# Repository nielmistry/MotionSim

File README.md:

# DIY Motion Simulator

This project provides a comprehensive guide to building a low-cost DIY motion simulator for flying RC planes and simulator games. Combining woodworking and mechatronics, it offers an affordable alternative to commercial options. The documentation includes CAD models, detailed assembly instructions, and software setup.

Support This Project: [Patreon](https://patreon.com/MichaelRechtin)

## Features
- Compatible with flight simulation games like Microsoft Flight Simulator 2020/2024 and WarThunder.
- Support for RC planes using ArduPilot.
- Modular design for portability, using a universal joint for base and chair connection.
- Open-source software and hardware design.

## Disclaimer
This is a DIY project; individual modifications may be necessary due to part availability or unique requirements. Ensure proper safety precautions, and consult professionals when needed. The author is not liable for any issues arising from the build.

## Getting Started
1. **CAD Models**: Access the full CAD design [here](https://cad.onshape.com/documents/14465a5308115755a641bf91/w/473302792caf9fe5237c9eca/e/42b5f99c290e18c70798f158?renderMode=0&uiState=67888ffc05482c0eb0b74d11).
2. **Bill of Materials**: Refer to the detailed parts list in the documentation for all required components.
3. **Tools Required**:
   - Saws (e.g., circular, jigsaw, CNC router)
   - Power drill, impact driver
   - Soldering iron, 3D printer

## Assembly
The simulator comprises two main parts:
- **Base Assembly**: Includes motor mounts, universal joint, and support structures.
- **Chair Assembly**: Features side panels, foot supports, and a universal joint for connection to the base.

Follow the detailed step-by-step instructions in the documentation.

## Electronics and Wiring
The wiring for the simulator includes:
- Motion base wiring for motors and drivers.
- Side compartment wiring for controller integration.
- Back panel connectors for ease of disassembly.

### Custom PCB Design
This repository includes a custom PCB design located in the `MotionSimPCB` directory that differs from the original project layout and provides several enhancements:

- **Power off button**: Integrated power control for safe system shutdown
- **Logic level translator**: Built-in voltage level conversion eliminating the need for external modules
- **Integrated MPU-6050 footprint**: Direct PCB mounting option for the motion sensor while maintaining compatibility with external MPU-6050 modules

The custom PCB maintains backward compatibility with the original wiring approach while offering a more integrated and robust solution.

Ensure proper orientation and connections for the MPU6050 sensor and other components.

## Software Setup
- **Teensy 4.0**: Flash the provided C++ code to control pitch and roll motors.
- **Raspberry Pi**: Configure USB flight controls and autorun scripts for seamless operation.
- **PC Integration**: Install necessary Python packages for supported games. Full code and instructions are available on the [GitHub repository](https://github.com/MichaelRechtin/MotionSim).

## Supported Games and Modes
- **Simulator Games**: Microsoft Flight Simulator 2020/2024, WarThunder
- **RC Planes**: Integration with Ardupilot and MAVLINK configurations

## Additional Features
- Optional integration with Buttkicker for enhanced gaming experience.
- Flexible wiring options for custom setups.

## Resources
- [Detailed Documentation](./DIY%20Motion%20Simulator%20Documentation.pdf)
- [PCB CI/CD Documentation](./docs/PCB_CI_CD.md) - Automated PCB manufacturing file generation
- [GitHub Repository](https://github.com/MichaelRechtin/MotionSim)
- [Bill of Materials](#)

### PCB Manufacturing

This repository includes automated CI/CD workflows for generating PCB manufacturing files:

- **Automated Gerber Generation**: Manufacturing files are automatically generated from KiCad PCB designs
- **Release Management**: Semantic versioning triggers automatic GitHub releases with PCB files
- **Local Generation**: Use `./generate-pcb-files.sh` to generate files locally

See [PCB CI/CD Documentation](./docs/PCB_CI_CD.md) for detailed information.

---

Feel free to explore, modify, and enjoy your DIY Motion Simulator!

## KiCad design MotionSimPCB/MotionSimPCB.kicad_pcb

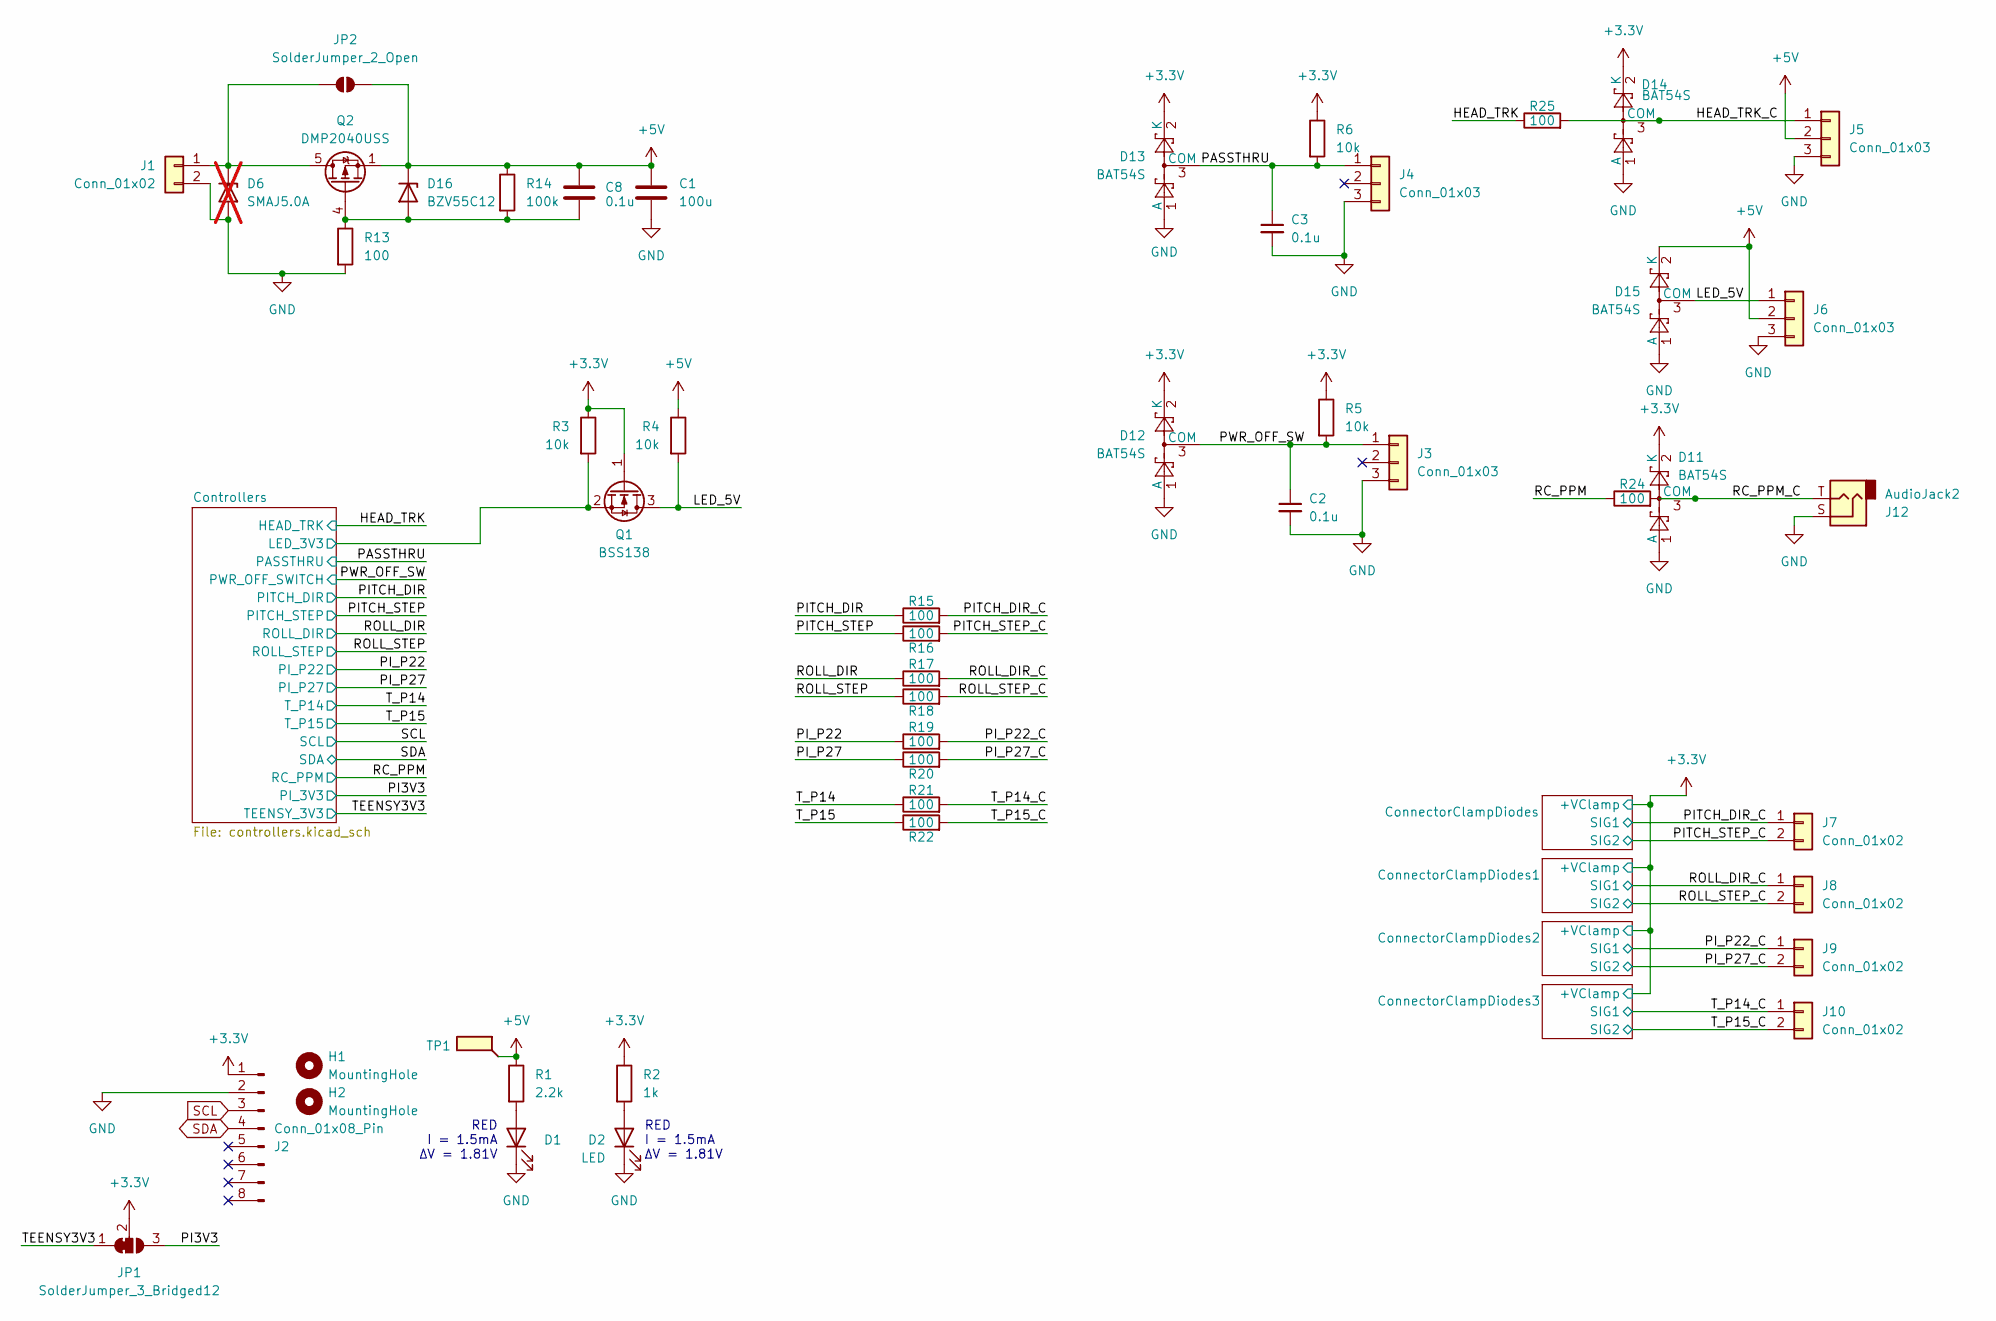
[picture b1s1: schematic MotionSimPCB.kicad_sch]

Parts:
C1: 100u; C_Radial_D6.3mm_H5.0mm_P2.50mm
C2, C3: 0.1u; C_0805_2012Metric
C8: 0.1u; C_0603_1608Metric
D1, D2: LED; D_0805_2012Metric; JLC PN C2286
D6: SMAJ5.0A; D_SMA; not fitted
D11, D12, D13, D14, D15: BAT54S; SOT-23
D16: BZV55C12; D_MiniMELF
H1, H2: MountingHole; MountingHole_2.7mm_M2.5
J1, J7, J8, J9, J10: Conn_01x02; TerminalBlock_Phoenix_MKDS-1,5-2_1x02_P5.00mm_Horizontal
J2: Conn_01x08_Pin; PinSocket_1x08_P2.54mm_Vertical
J3, J4, J5, J6: Conn_01x03; JST_XH_B3B-XH-AM_1x03_P2.50mm_Vertical
J12: AudioJack2
JP1: SolderJumper_3_Bridged12; SolderJumper-3_P1.3mm_Bridged2Bar12_RoundedPad1.0x1.5mm
JP2: SolderJumper_2_Open; SolderJumper-2_P1.3mm_Open_TrianglePad1.0x1.5mm
Q1: BSS138; SOT-23
Q2: DMP2040USS; SOIC-8_3.9x4.9mm_P1.27mm
R1: 2.2k; R_0805_2012Metric
R2: 1k; R_0805_2012Metric
R3, R4, R5, R6: 10k; R_0805_2012Metric
R13, R15, R16, R17, R18, R19, R20, R21, R22, R24, R25: 100; C_0603_1608Metric
R14: 100k; C_0603_1608Metric
TP1: TestPoint_Flag; TestPoint_Pad_D2.0mm

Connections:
+3.3V: D11.2 (K), D12.2 (K), D13.2 (K), D14.2 (K), J2.1, JP1.2 (C), Q1.1 (G), R2.1, R3.1, R5.1, R6.1; also elsewhere on the board
+5V: C1.1, C8.1, D15.2 (K), D16.1 (K), J5.2, J6.2, JP2.2 (B), Q2.1 (S), Q2.2 (S), Q2.3 (S), R1.1, R4.1, R14.1, TP1.1; also elsewhere on the board
/Controllers/LED_3V3: Q1.2 (S), R3.2; also elsewhere on the board
/HEAD_TRK: R25.1; also elsewhere on the board
/HEAD_TRK_C: D14.3 (COM), J5.1, R25.2
/LED_5V: D15.3 (COM), J6.1, Q1.3 (D), R4.2
/PASSTHRU: C3.1, D13.3 (COM), J4.1, R6.2; also elsewhere on the board
/PI3V3: JP1.3 (B); also elsewhere on the board
/PITCH_DIR: R15.1; also elsewhere on the board
/PITCH_DIR_C: J7.1, R15.2; also elsewhere on the board
/PITCH_STEP: R16.1; also elsewhere on the board
/PITCH_STEP_C: J7.2, R16.2; also elsewhere on the board
/PI_P22: R19.1; also elsewhere on the board
/PI_P22_C: J9.1, R19.2; also elsewhere on the board
/PI_P27: R20.1; also elsewhere on the board
/PI_P27_C: J9.2, R20.2; also elsewhere on the board
/PWR_OFF_SW: C2.1, D12.3 (COM), J3.1, R5.2; also elsewhere on the board
/RC_PPM: R24.1; also elsewhere on the board
/RC_PPM_C: D11.3 (COM), J12.T, R24.2
/ROLL_DIR: R17.1; also elsewhere on the board
/ROLL_DIR_C: J8.1, R17.2; also elsewhere on the board
/ROLL_STEP: R18.1; also elsewhere on the board
/ROLL_STEP_C: J8.2, R18.2; also elsewhere on the board
/TEENSY3V3: JP1.1 (A); also elsewhere on the board
/T_P14: R21.1; also elsewhere on the board
/T_P14_C: J10.1, R21.2; also elsewhere on the board
/T_P15: R22.1; also elsewhere on the board
/T_P15_C: J10.2, R22.2; also elsewhere on the board
GND: C1.2, C2.2, C3.2, D1.1 (K), D2.1 (K), D6.2 (A2), D11.1 (A), D12.1 (A), D13.1 (A), D14.1 (A), D15.1 (A), J1.2, J2.2, J3.3, J4.3, J5.3, J6.3, J12.S, R13.2; also elsewhere on the board
unnamed: D1.2 (A), R1.2
unnamed: D2.2 (A), R2.2
unnamed: D6.1 (A1), J1.1, JP2.1 (A), Q2.5 (D), Q2.6 (D), Q2.7 (D), Q2.8 (D)
unnamed: C8.2, D16.2 (A), Q2.4 (G), R13.1, R14.2
SCL: J2.3; also elsewhere on the board
SDA: J2.4; also elsewhere on the board

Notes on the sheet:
RED I = 1.5mA ΔV = 1.81V

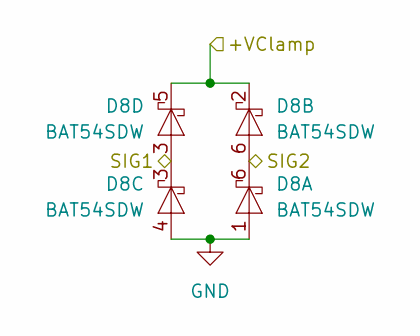
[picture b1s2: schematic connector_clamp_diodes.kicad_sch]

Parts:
D8: BAT54SDW; SOT-363_SC-70-6

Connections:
+3.3V: D8.2 (K), D8.5 (K); also elsewhere on the board
/PITCH_DIR_C: D8.3 (K); also elsewhere on the board
/PITCH_STEP_C: D8.6 (K); also elsewhere on the board
GND: D8.1 (A), D8.4 (A); also elsewhere on the board

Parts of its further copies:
D7, D9, D10: BAT54SDW; SOT-363_SC-70-6

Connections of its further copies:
+3.3V: D7.2 (K), D7.5 (K), D9.2 (K), D9.5 (K), D10.2 (K), D10.5 (K); also elsewhere on the board
/PI_P22_C: D9.3 (K); also elsewhere on the board
/PI_P27_C: D9.6 (K); also elsewhere on the board
/ROLL_DIR_C: D7.3 (K); also elsewhere on the board
/ROLL_STEP_C: D7.6 (K); also elsewhere on the board
/T_P14_C: D10.3 (K); also elsewhere on the board
/T_P15_C: D10.6 (K); also elsewhere on the board
GND: D7.1 (A), D7.4 (A), D9.1 (A), D9.4 (A), D10.1 (A), D10.4 (A); also elsewhere on the board

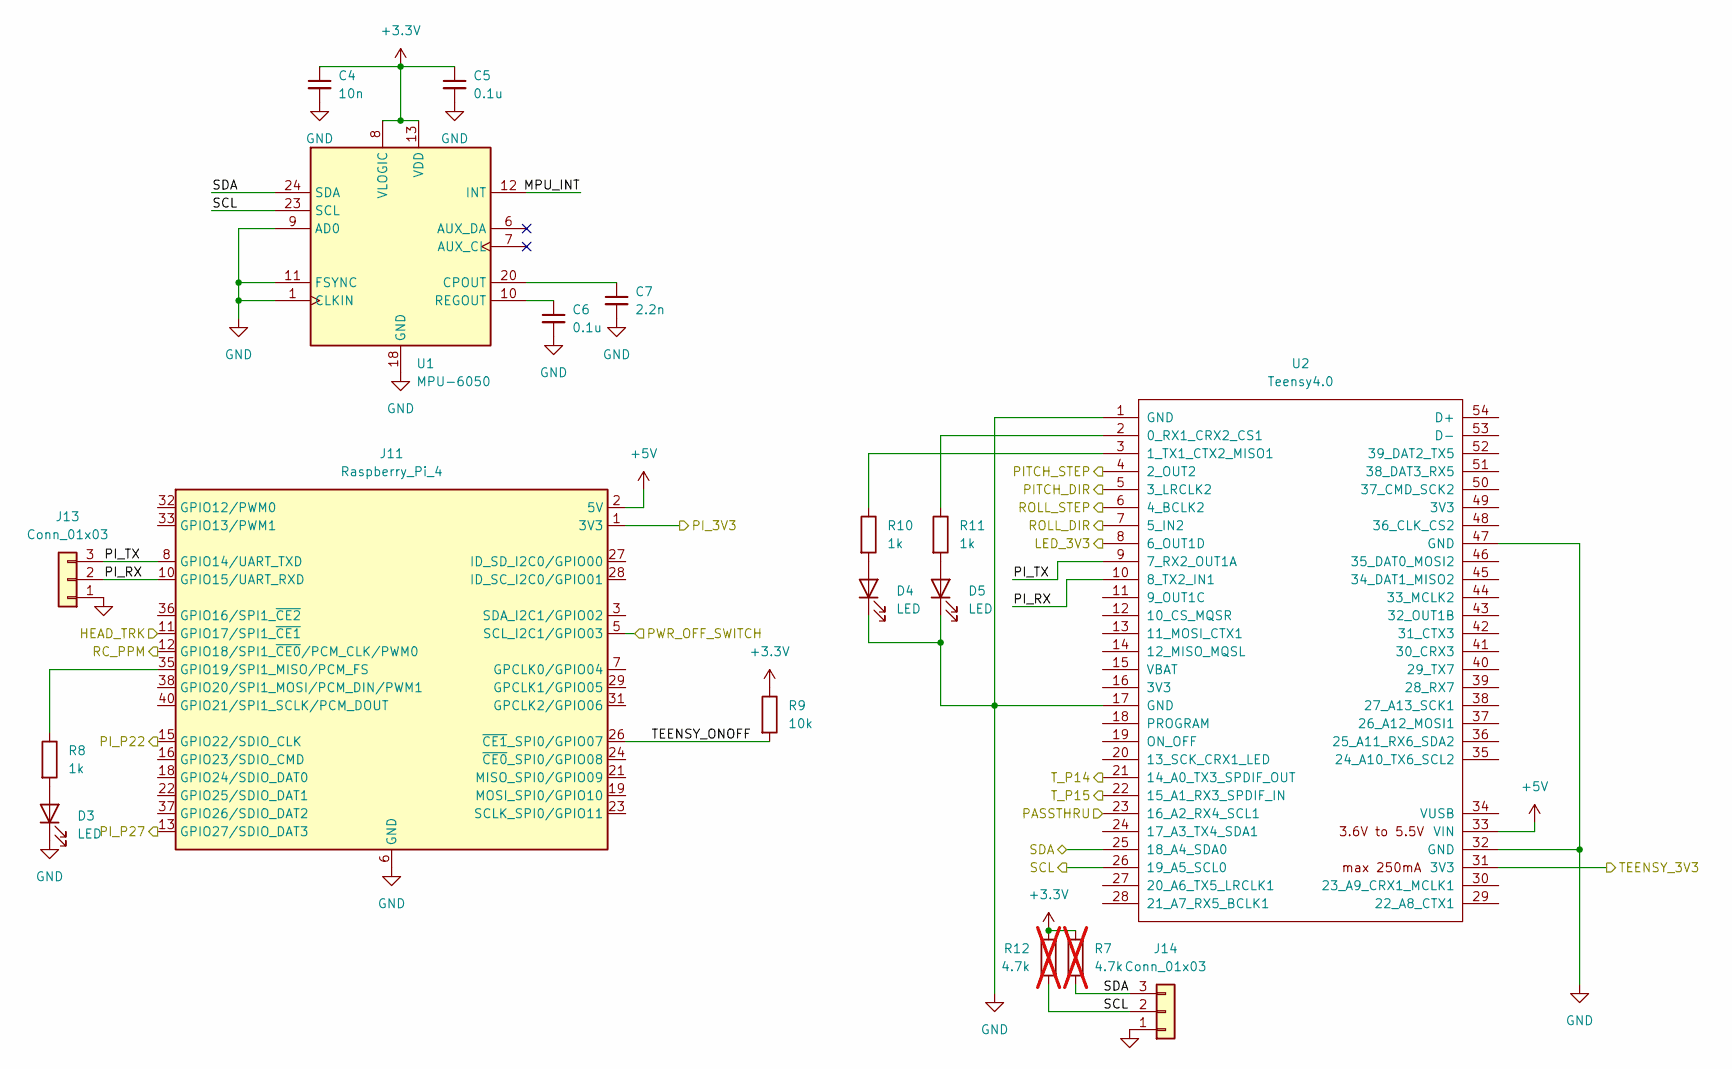
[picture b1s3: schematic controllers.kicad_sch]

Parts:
C4: 10n; C_0603_1608Metric
C5, C6: 0.1u; C_0603_1608Metric
C7: 2.2n; C_0603_1608Metric
D3, D4, D5: LED; D_0805_2012Metric; JLC PN C2289
J11: Raspberry_Pi_4; raspberrypi_2_3
J13, J14: Conn_01x03; PinHeader_1x03_P2.54mm_Vertical
R7, R12: 4.7k; R_0805_2012Metric; not fitted
R8, R10, R11: 1k; R_0805_2012Metric
R9: 10k; R_0805_2012Metric
U1: MPU-6050; InvenSense_QFN-24_4x4mm_P0.5mm
U2: Teensy4.0; Teensy40

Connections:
+3.3V: C4.1, C5.1, R7.1, R9.1, R12.1, U1.8 (VLOGIC), U1.13 (VDD); also elsewhere on the board
+5V: J11.2 (5V), J11.4 (5V), U2.33 (VIN); also elsewhere on the board
/Controllers/LED_3V3: U2.8 (6_OUT1D); also elsewhere on the board
/Controllers/MPU_INT: U1.12 (INT)
/Controllers/PI_RX: J11.10 (GPIO15/UART_RXD), J13.2, U2.10 (8_TX2_IN1)
/Controllers/PI_TX: J11.8 (GPIO14/UART_TXD), J13.3, U2.9 (7_RX2_OUT1A)
/Controllers/TEENSY_ONOFF: J11.26 (~CE1_SPI0/GPIO07), R9.2
/HEAD_TRK: J11.11 (GPIO17/SPI1_~CE1); also elsewhere on the board
/PASSTHRU: U2.23 (16_A2_RX4_SCL1); also elsewhere on the board
/PI3V3: J11.1 (3V3), J11.17 (3V3); also elsewhere on the board
/PITCH_DIR: U2.5 (3_LRCLK2); also elsewhere on the board
/PITCH_STEP: U2.4 (2_OUT2); also elsewhere on the board
/PI_P22: J11.15 (GPIO22/SDIO_CLK); also elsewhere on the board
/PI_P27: J11.13 (GPIO27/SDIO_DAT3); also elsewhere on the board
/PWR_OFF_SW: J11.5 (SCL_I2C1/GPIO03); also elsewhere on the board
/RC_PPM: J11.12 (GPIO18/SPI1_~CE0/PCM_CLK/PWM0); also elsewhere on the board
/ROLL_DIR: U2.7 (5_IN2); also elsewhere on the board
/ROLL_STEP: U2.6 (4_BCLK2); also elsewhere on the board
/TEENSY3V3: U2.31 (3V3); also elsewhere on the board
/T_P14: U2.21 (14_A0_TX3_SPDIF_OUT); also elsewhere on the board
/T_P15: U2.22 (15_A1_RX3_SPDIF_IN); also elsewhere on the board
GND: C4.2, C5.2, C6.2, C7.2, D3.1 (K), D4.1 (K), D5.1 (K), J11.6 (GND), J11.9 (GND), J11.14 (GND), J11.20 (GND), J11.25 (GND), J11.30 (GND), J11.34 (GND), J11.39 (GND), J13.1, J14.1, U1.1 (CLKIN), U1.9 (AD0), U1.11 (FSYNC), U1.18 (GND), U2.1 (GND), U2.17 (GND), U2.32 (GND), U2.47 (GND); also elsewhere on the board
unnamed: D3.2 (A), R8.2
unnamed: D4.2 (A), R10.2
unnamed: D5.2 (A), R11.2
unnamed: J11.35 (GPIO19/SPI1_MISO/PCM_FS), R8.1
unnamed: C7.1, U1.20 (CPOUT)
unnamed: C6.1, U1.10 (REGOUT)
unnamed: R11.1, U2.2 (0_RX1_CRX2_CS1)
unnamed: R10.1, U2.3 (1_TX1_CTX2_MISO1)
SCL: J14.2, R12.2, U1.23 (SCL), U2.26 (19_A5_SCL0); also elsewhere on the board
SDA: J14.3, R7.2, U1.24 (SDA), U2.25 (18_A4_SDA0); also elsewhere on the board

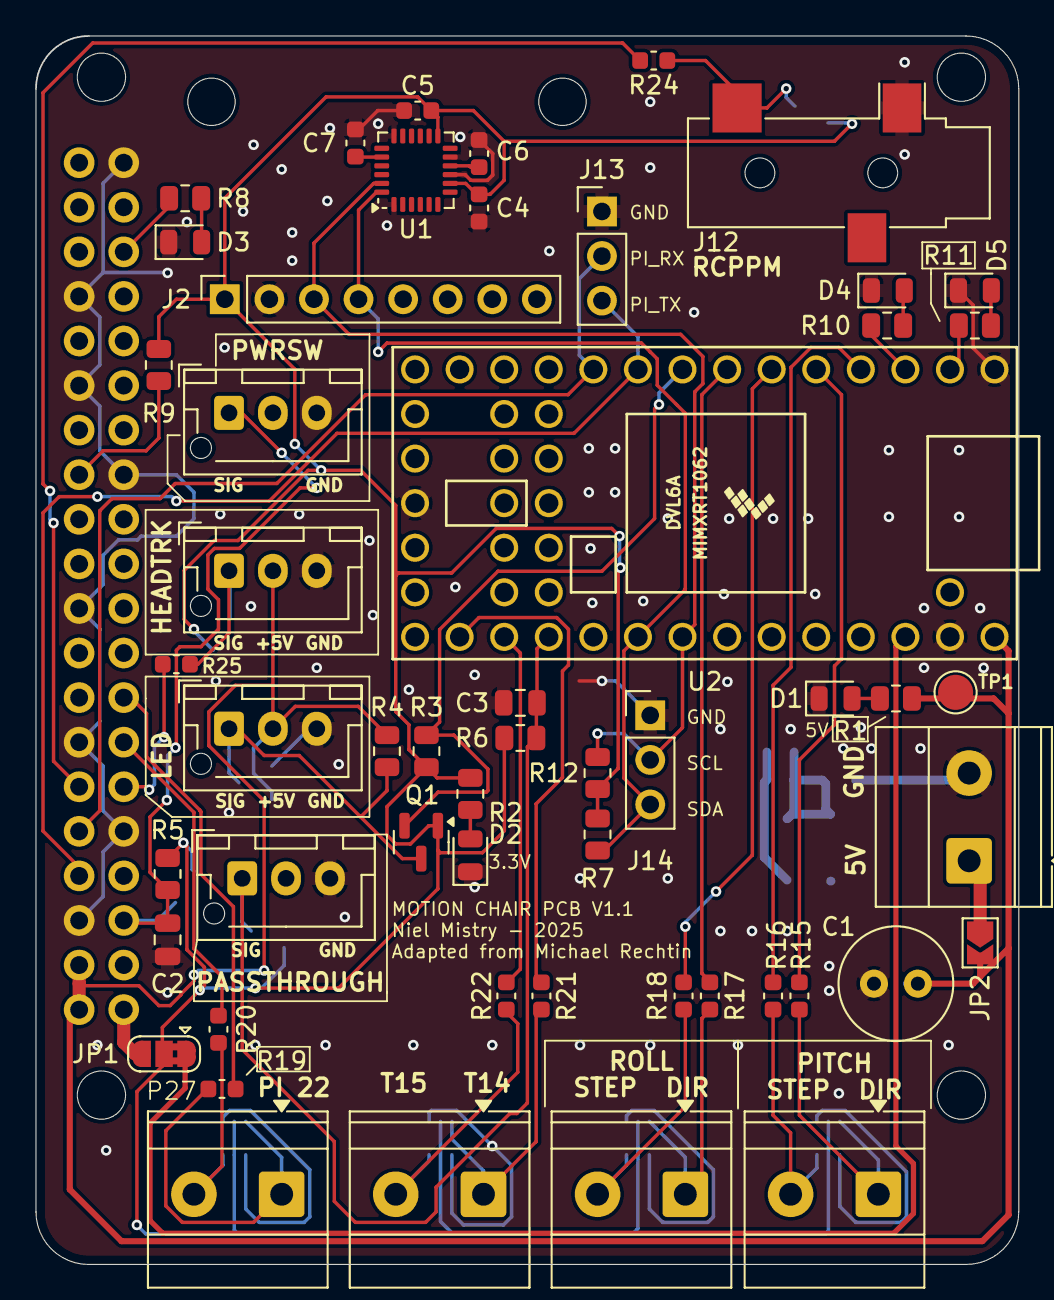
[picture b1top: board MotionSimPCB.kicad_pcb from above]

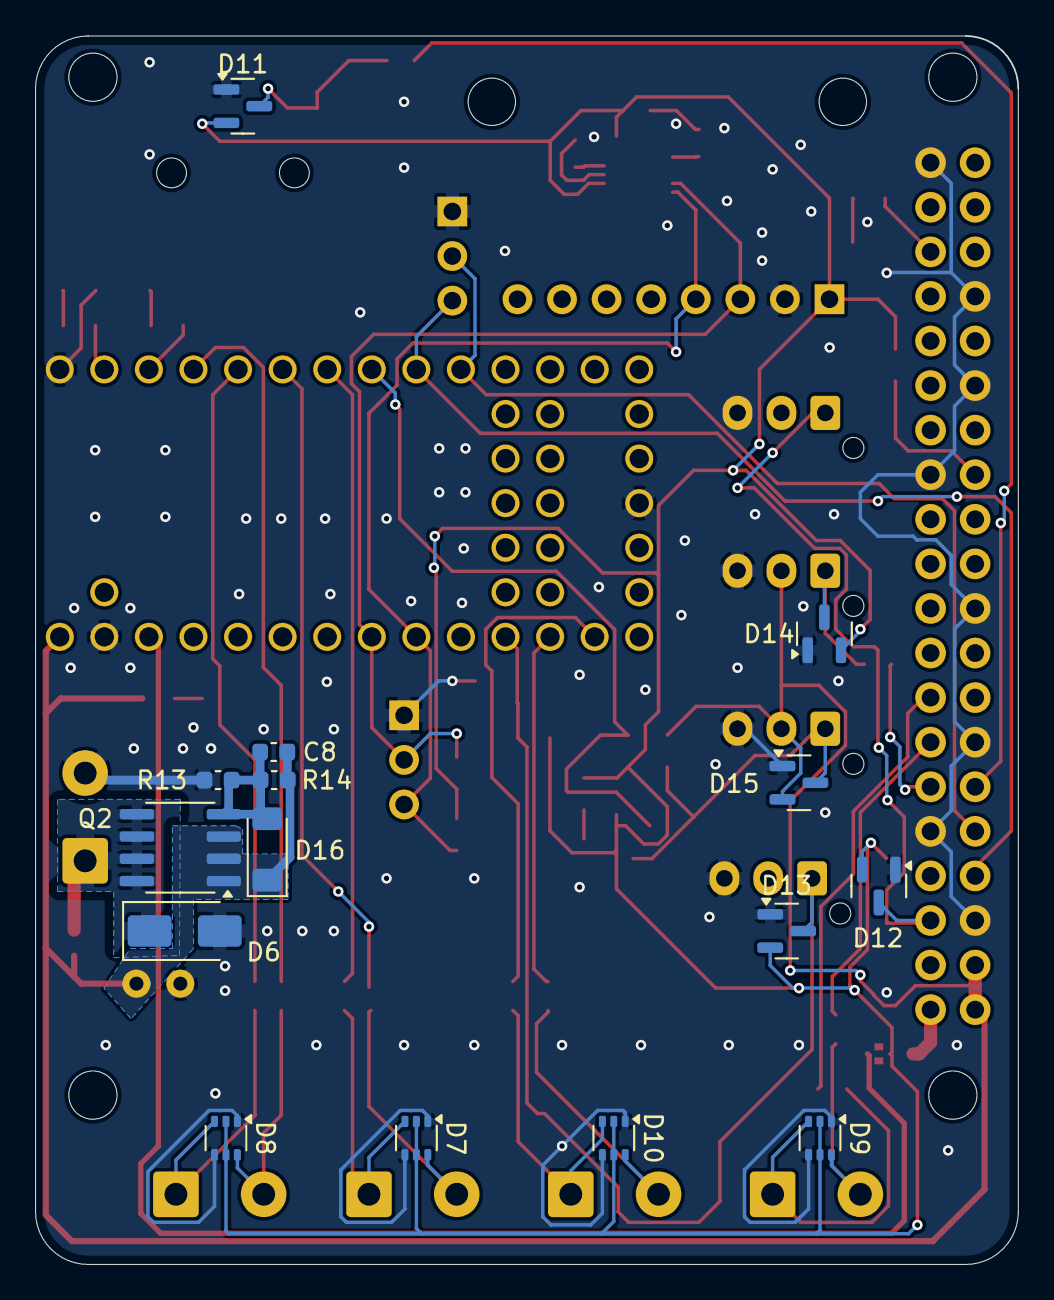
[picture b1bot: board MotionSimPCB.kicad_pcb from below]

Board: 2 copper layers, 56.0 x 70.0 mm, 71 parts (15 on the bottom side), 46 nets.

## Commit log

2025-08-26 first commit of pcb
2025-08-26 Initial plan
2025-08-26 Add custom PCB information to README Electronics section
2025-08-26 round corners
2025-08-26 cleanup silkscreen
2025-08-28 fix drc, add protection
2025-08-28 fix some issues
2025-08-28 Add GitHub Actions workflows for PCB CI/CD
2025-08-28 Fix PCB file generation and artifact URL issues
2025-08-28 Rebase on PCB branch and update workflow targets
2025-08-28 Fix YAML syntax in test workflow
2025-08-28 Implement robust PCB CI/CD with fallback mechanisms
2025-08-28 Add comprehensive documentation and final improvements
2025-08-28 Apply suggestion from @nielmistry
2025-08-30 fix clearance
2025-08-30 Update tag pattern for semantic versioning
2025-09-04 DNP D6
